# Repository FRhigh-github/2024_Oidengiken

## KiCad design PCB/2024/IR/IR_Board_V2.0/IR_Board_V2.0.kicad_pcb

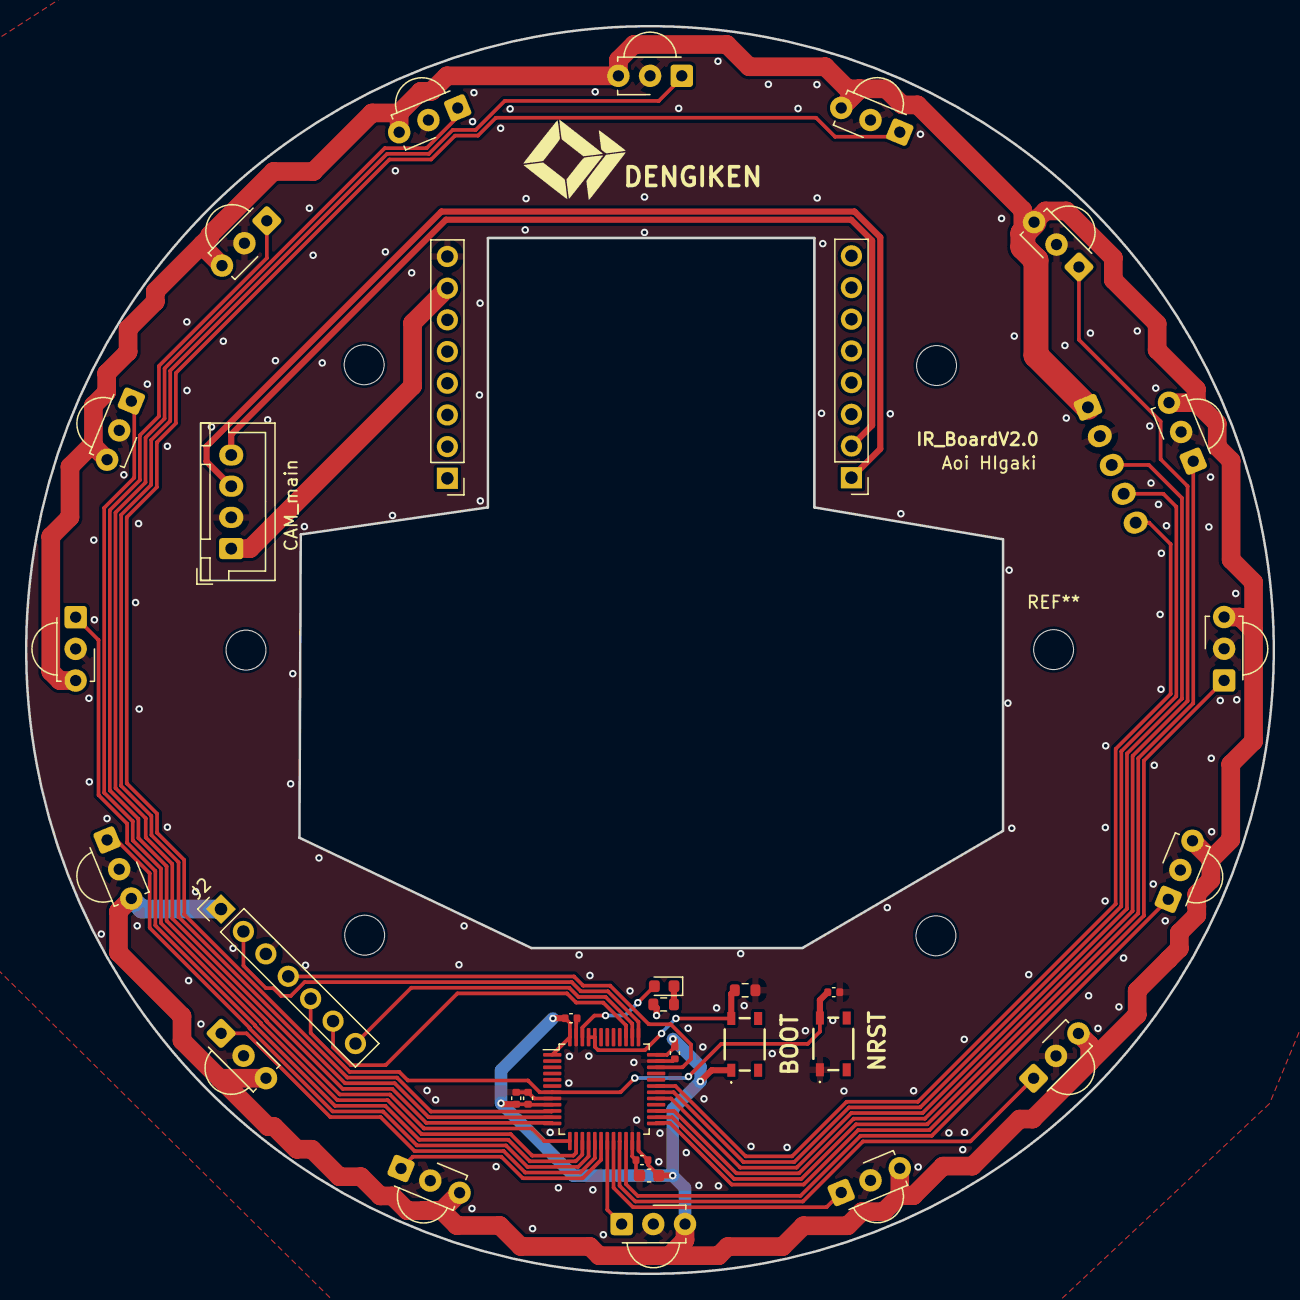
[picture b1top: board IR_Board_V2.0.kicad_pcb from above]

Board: 2 copper layers, 100.0 x 100.0 mm, 34 parts (1 on the bottom side), 32 nets.

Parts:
BOOT: BOOT; SKRPABE010
C1, C3, C5, C7: 0.1u; C_0402_1005Metric
C2: 0.01u; C_0402_1005Metric
C4: 1u; C_0402_1005Metric
C6: 4.7uf; C_0603_1608Metric
CAM_main: Conn_01x04_Socket; JST_XH_B4B-XH-A_1x04_P2.50mm_Vertical
D1: LED; LED_0603_1608Metric
IR_Main: Main,IR; JST_XH_B5B-XH-A_1x05_P2.50mm_Vertical
J2: PC; PinHeader_1x07_P2.54mm_Vertical
J4, J5: Conn_01x08_Male; PinHeader_1x08_P2.54mm_Vertical
NRST: NRST; SKRPABE010
R3: 100; R_0603_1608Metric
R4: R_Small; R_0603_1608Metric
U1: STM32F303C8Tx; LQFP-48_7x7mm_P0.5mm
U2, U3, U4, U5, U6, U7, U8, U9, U10, U11, U12, U13, U14, U15, U16, U17: TSSP58038; Vishay_MINICAST-3Pin

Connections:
+3.3V: BOOT.1, C1.1, C2.1, C3.1, C4.1, C5.1, C6.1, IR_Main.1, J2.1, U1.1 (VBAT), U1.9 (VDDA), U1.24 (VDD), U1.36 (VDD), U1.48 (VDD), U2.3 (Vs), U3.3 (Vs), U4.3 (Vs), U5.3 (Vs), U6.3 (Vs), U7.3 (Vs), U8.3 (Vs), U9.3 (Vs), U10.3 (Vs), U11.3 (Vs), U12.3 (Vs), U13.3 (Vs), U14.3 (Vs), U15.3 (Vs), U16.3 (Vs), U17.3 (Vs)
+5V: CAM_main.1, J5.7
BOOT: BOOT.2, R4.1, U1.44 (BOOT0), U1.45 (PB8)
CAMRX: CAM_main.3, J4.1
CAMTX: CAM_main.4, J4.2
GND: C1.2, C2.2, C3.2, C4.2, C5.2, C6.2, C7.2, CAM_main.2, IR_Main.2, J2.3, J5.8, NRST.1, R3.2, R4.2, U1.8 (VSSA), U1.23 (VSS), U1.35 (VSS), U1.47 (VSS), U2.2 (GND), U3.2 (GND), U4.2 (GND), U5.2 (GND), U6.2 (GND), U7.2 (GND), U8.2 (GND), U9.2 (GND), U10.2 (GND), U11.2 (GND), U12.2 (GND), U13.2 (GND), U14.2 (GND), U15.2 (GND), U16.2 (GND), U17.2 (GND)
GPIO0: U1.10 (PA0), U9.1 (OUT)
GPIO1: U1.11 (PA1), U2.1 (OUT)
GPIO2: U1.12 (PA2), U8.1 (OUT)
GPIO3: U1.13 (PA3), U6.1 (OUT)
GPIO4: U1.14 (PA4), U7.1 (OUT)
GPIO5: U1.15 (PA5), U3.1 (OUT)
GPIO6: U1.16 (PA6), U17.1 (OUT)
GPIO7: U1.17 (PA7), U16.1 (OUT)
GPIO8: U1.18 (PB0), U15.1 (OUT)
GPIO9: U1.19 (PB1), U4.1 (OUT)
GPIO10: U1.20 (PB2), U14.1 (OUT)
GPIO11: U1.21 (PB10), U13.1 (OUT)
GPIO12: U1.22 (PB11), U12.1 (OUT)
GPIO13: U1.25 (PB12), U5.1 (OUT)
GPIO14: U1.26 (PB13), U11.1 (OUT)
GPIO15: U1.27 (PB14), U10.1 (OUT)
NRST: C7.1, J2.5, NRST.2, U1.7 (NRST)
unnamed: D1.1 (K), R3.1
SWCLK: J2.2, U1.37 (PA14)
SWDIO: J2.4, U1.34 (PA13)
UI_LED: D1.2 (A), U1.46 (PB9)
USART1_CK: IR_Main.3, U1.29 (PA8)
USART1_RX: IR_Main.5, U1.31 (PA10)
USART1_TX: IR_Main.4, U1.30 (PA9)
USART2_RX: J2.7, U1.38 (PA15)
USART2_TX: J2.6, U1.39 (PB3)

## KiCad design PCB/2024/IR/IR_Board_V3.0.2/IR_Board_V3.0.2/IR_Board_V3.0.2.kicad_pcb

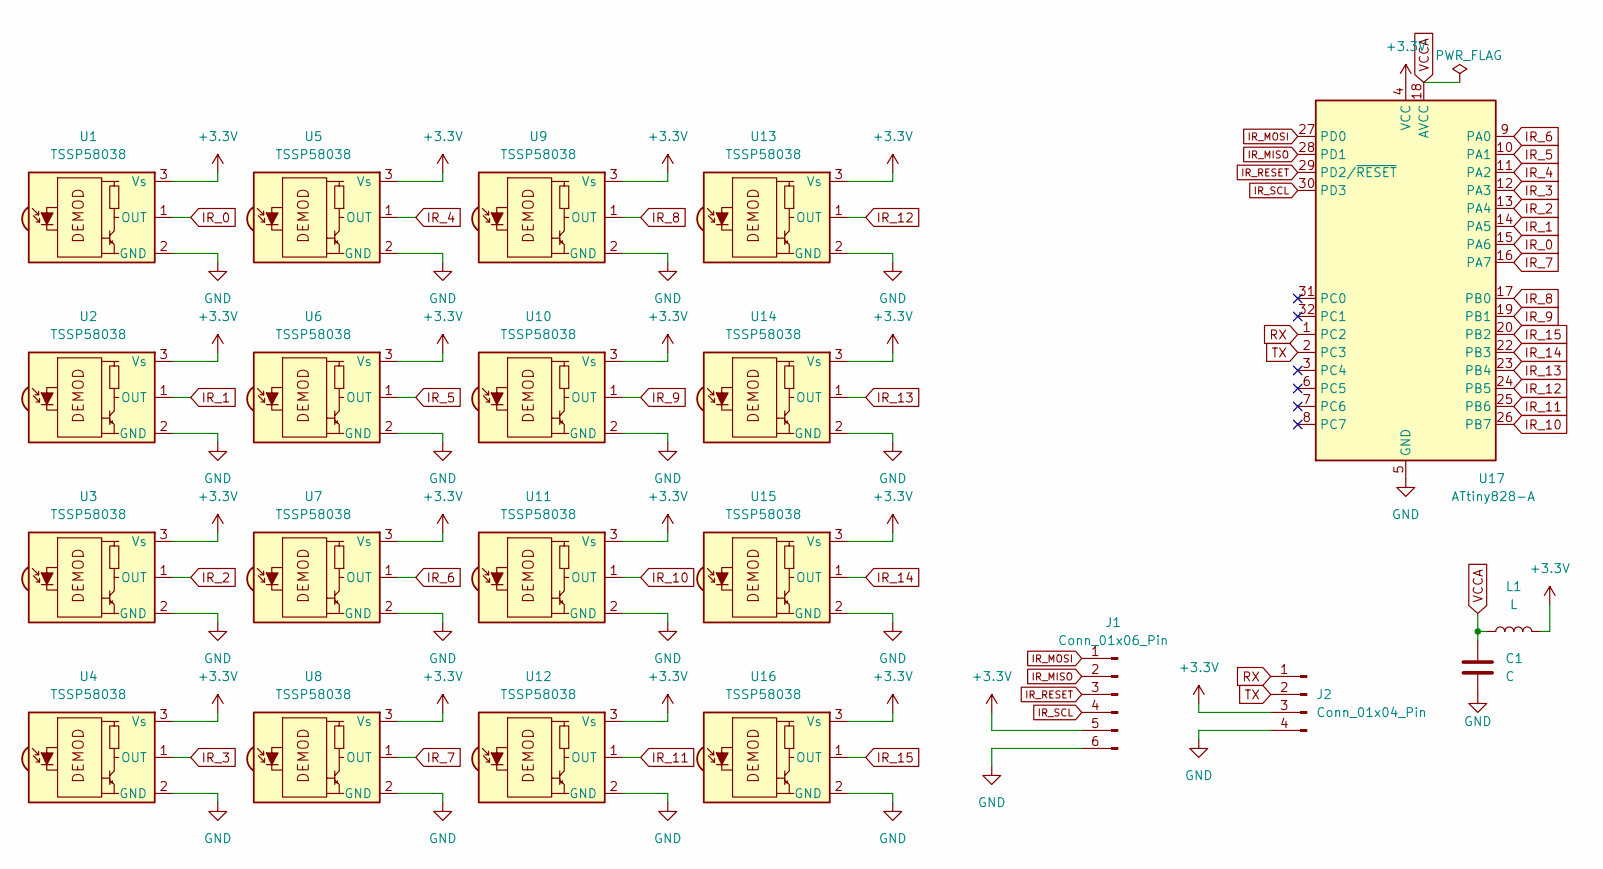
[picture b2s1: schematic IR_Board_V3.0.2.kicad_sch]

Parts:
C1: C; C_0603_1608Metric
J1: Conn_01x06_Pin; PinHeader_1x06_P2.54mm_Horizontal
J2: Conn_01x04_Pin; JST_XH_B4B-XH-A_1x04_P2.50mm_Vertical
L1: L; L_Axial_L12.0mm_D5.0mm_P15.24mm_Horizontal_Fastron_MISC
U1, U2, U3, U4, U5, U6, U7, U8, U9, U10, U11, U12, U13, U14, U15, U16: TSSP58038; Vishay_MINICAST-3Pin
U17: ATtiny828-A; TQFP-32_7x7mm_P0.8mm

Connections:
+3.3V: J1.5, J2.3, L1.2, U1.3 (Vs), U2.3 (Vs), U3.3 (Vs), U4.3 (Vs), U5.3 (Vs), U6.3 (Vs), U7.3 (Vs), U8.3 (Vs), U9.3 (Vs), U10.3 (Vs), U11.3 (Vs), U12.3 (Vs), U13.3 (Vs), U14.3 (Vs), U15.3 (Vs), U16.3 (Vs), U17.4 (VCC)
GND: C1.2, J1.6, J2.4, U1.2 (GND), U2.2 (GND), U3.2 (GND), U4.2 (GND), U5.2 (GND), U6.2 (GND), U7.2 (GND), U8.2 (GND), U9.2 (GND), U10.2 (GND), U11.2 (GND), U12.2 (GND), U13.2 (GND), U14.2 (GND), U15.2 (GND), U16.2 (GND), U17.5 (GND), U17.21 (GND)
IR_0: U1.1 (OUT), U17.15 (PA6)
IR_1: U2.1 (OUT), U17.14 (PA5)
IR_2: U3.1 (OUT), U17.13 (PA4)
IR_3: U4.1 (OUT), U17.12 (PA3)
IR_4: U5.1 (OUT), U17.11 (PA2)
IR_5: U6.1 (OUT), U17.10 (PA1)
IR_6: U7.1 (OUT), U17.9 (PA0)
IR_7: U8.1 (OUT), U17.16 (PA7)
IR_8: U9.1 (OUT), U17.17 (PB0)
IR_9: U10.1 (OUT), U17.19 (PB1)
IR_10: U11.1 (OUT), U17.26 (PB7)
IR_11: U12.1 (OUT), U17.25 (PB6)
IR_12: U13.1 (OUT), U17.24 (PB5)
IR_13: U14.1 (OUT), U17.23 (PB4)
IR_14: U15.1 (OUT), U17.22 (PB3)
IR_15: U16.1 (OUT), U17.20 (PB2)
IR_MISO: J1.2, U17.28 (PD1)
IR_MOSI: J1.1, U17.27 (PD0)
IR_RESET: J1.3, U17.29 (PD2/~RESET)
IR_SCL: J1.4, U17.30 (PD3)
RX: J2.1, U17.1 (PC2)
TX: J2.2, U17.2 (PC3)
VCCA: C1.1, L1.1, U17.18 (AVCC)

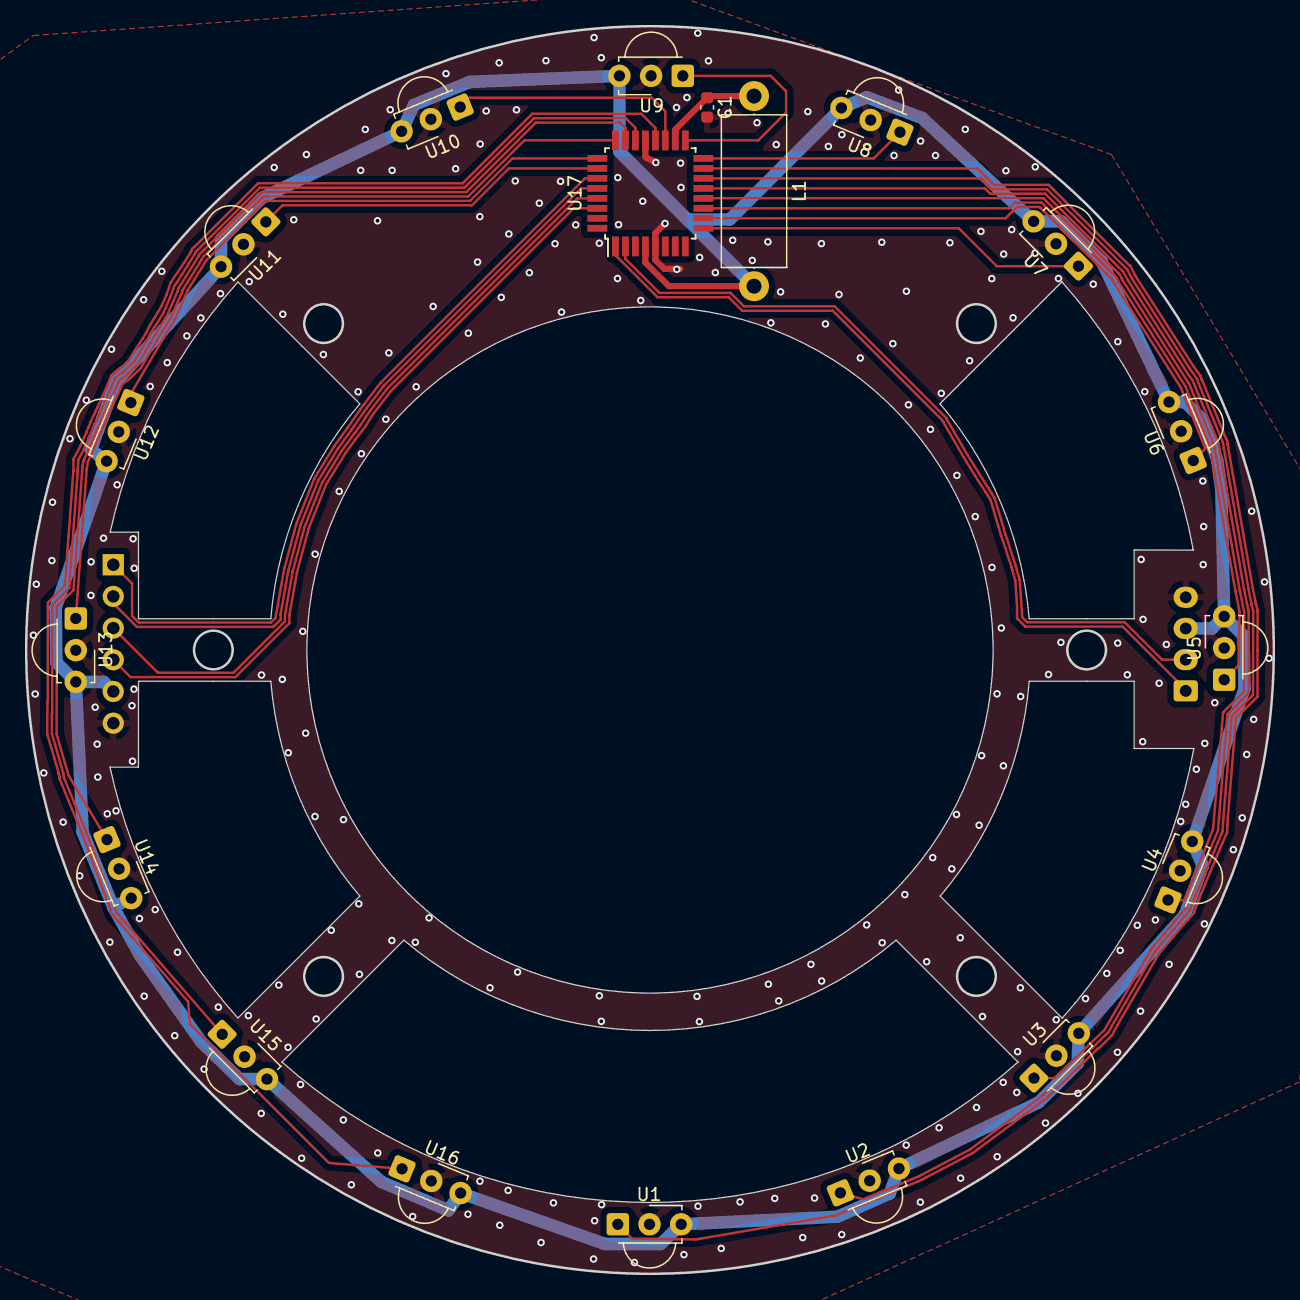
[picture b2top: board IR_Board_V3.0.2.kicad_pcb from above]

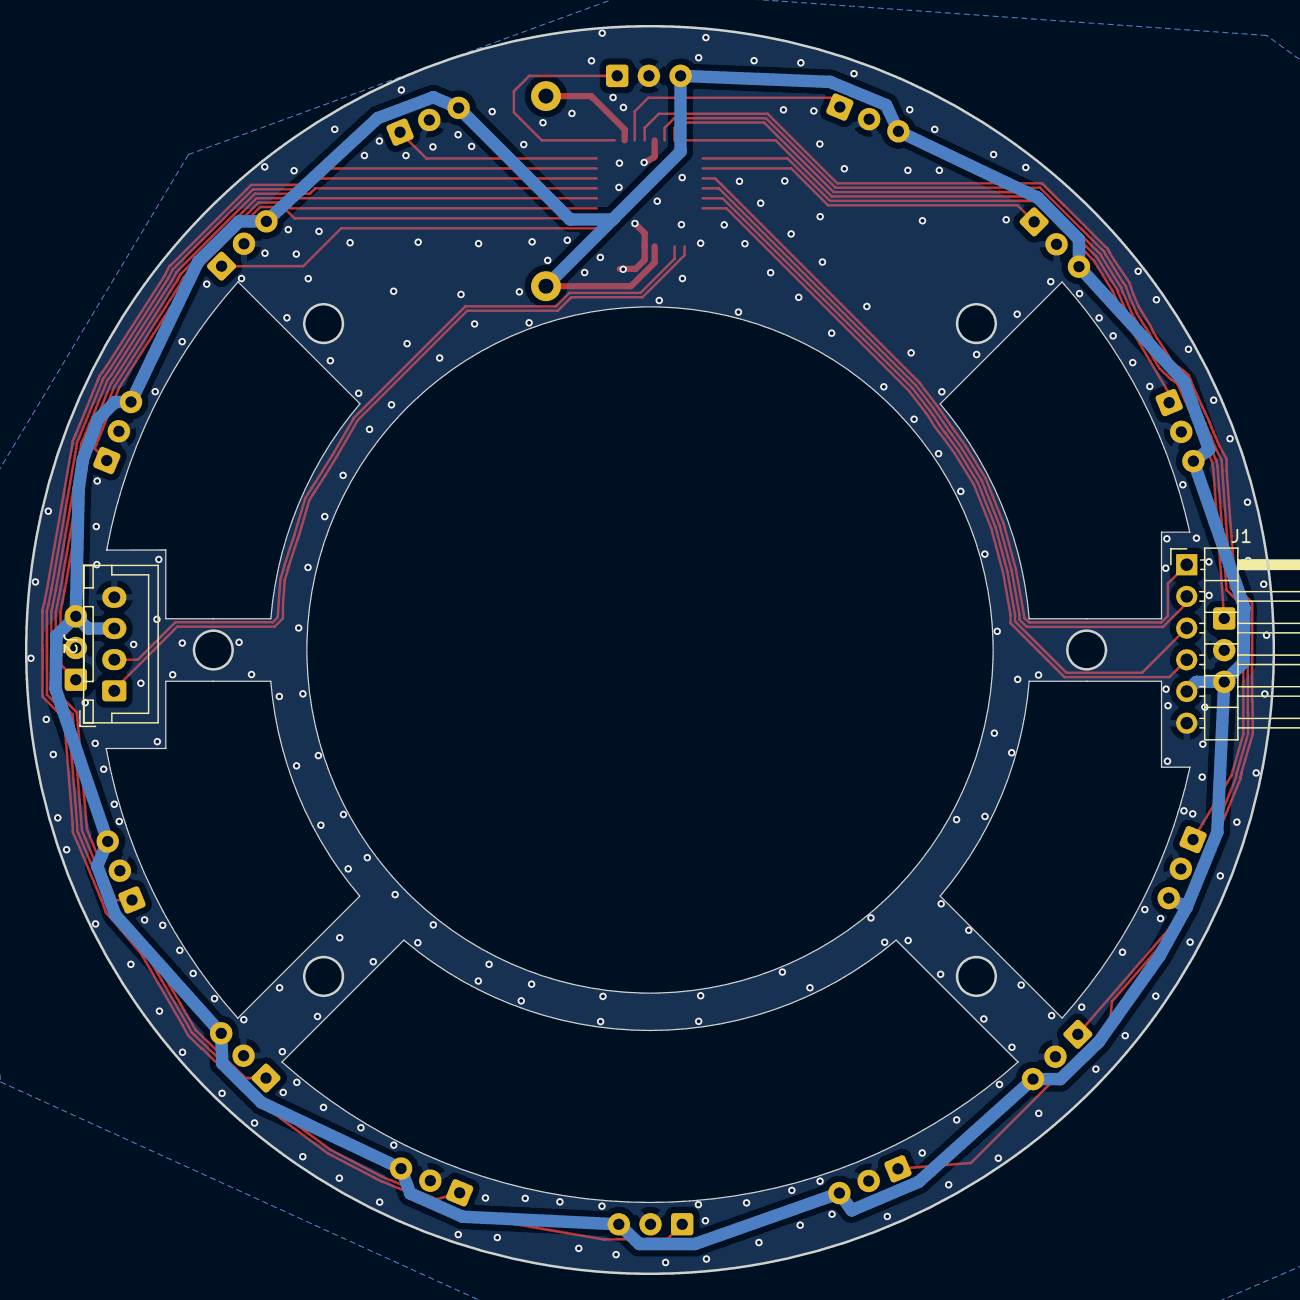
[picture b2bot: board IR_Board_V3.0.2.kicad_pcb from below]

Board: 2 copper layers, 100.0 x 100.0 mm, 21 parts (2 on the bottom side), 25 nets.

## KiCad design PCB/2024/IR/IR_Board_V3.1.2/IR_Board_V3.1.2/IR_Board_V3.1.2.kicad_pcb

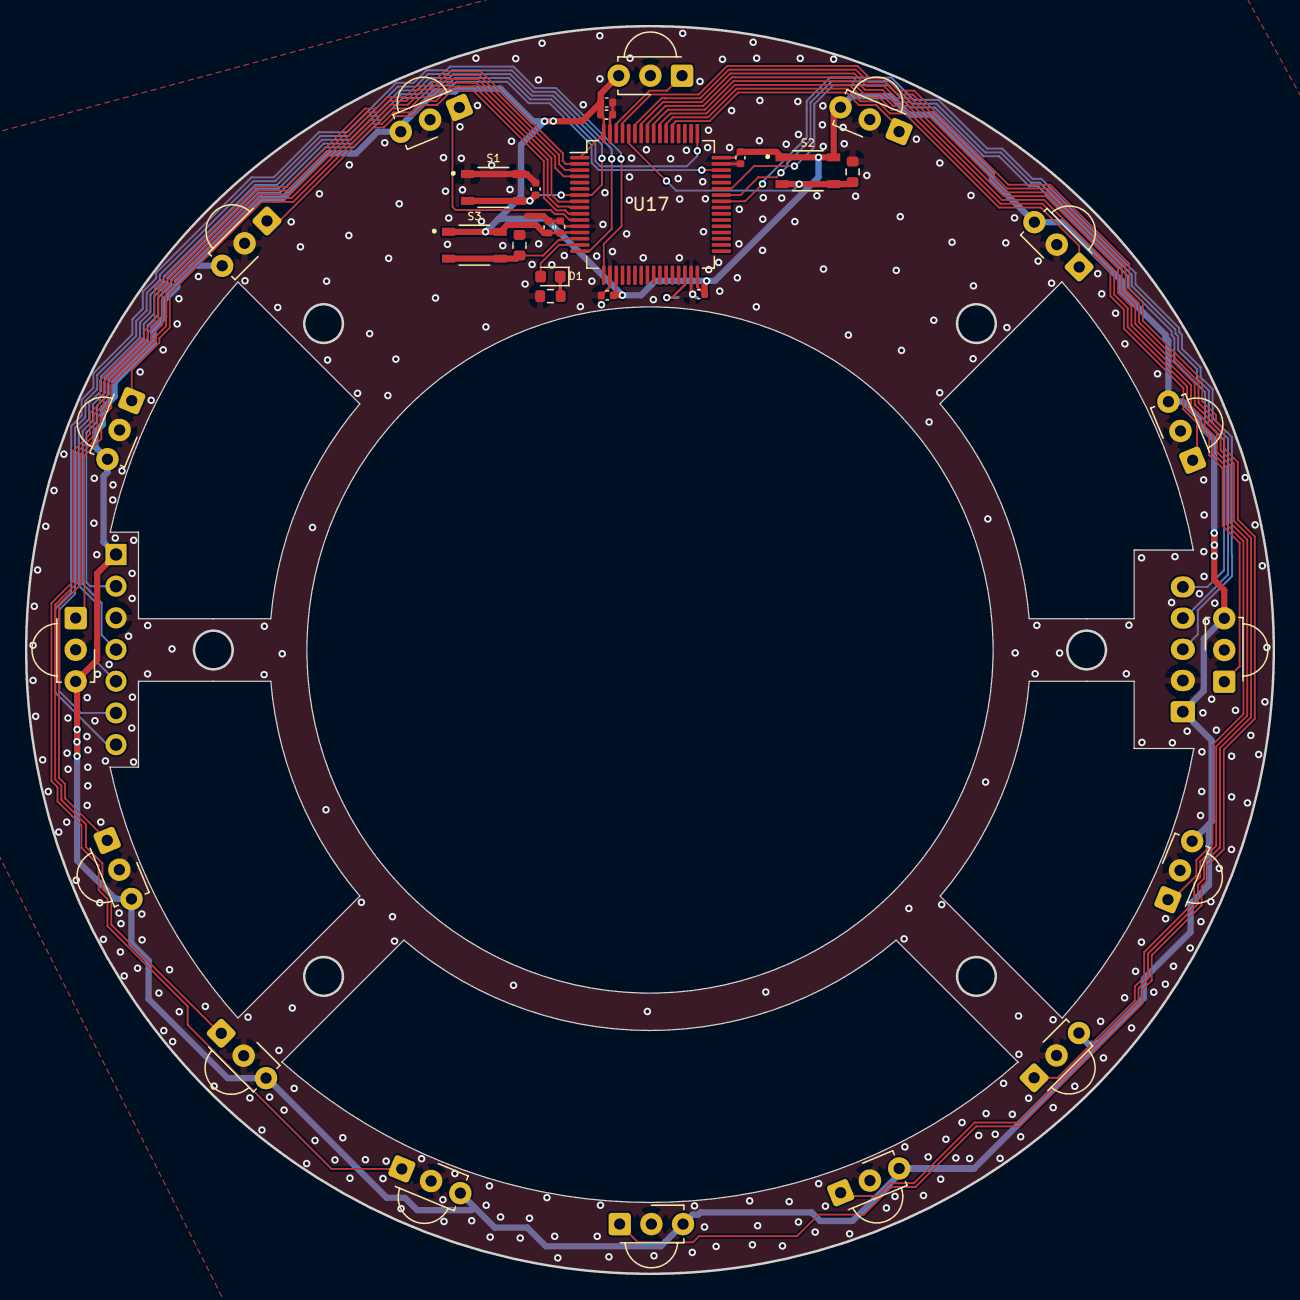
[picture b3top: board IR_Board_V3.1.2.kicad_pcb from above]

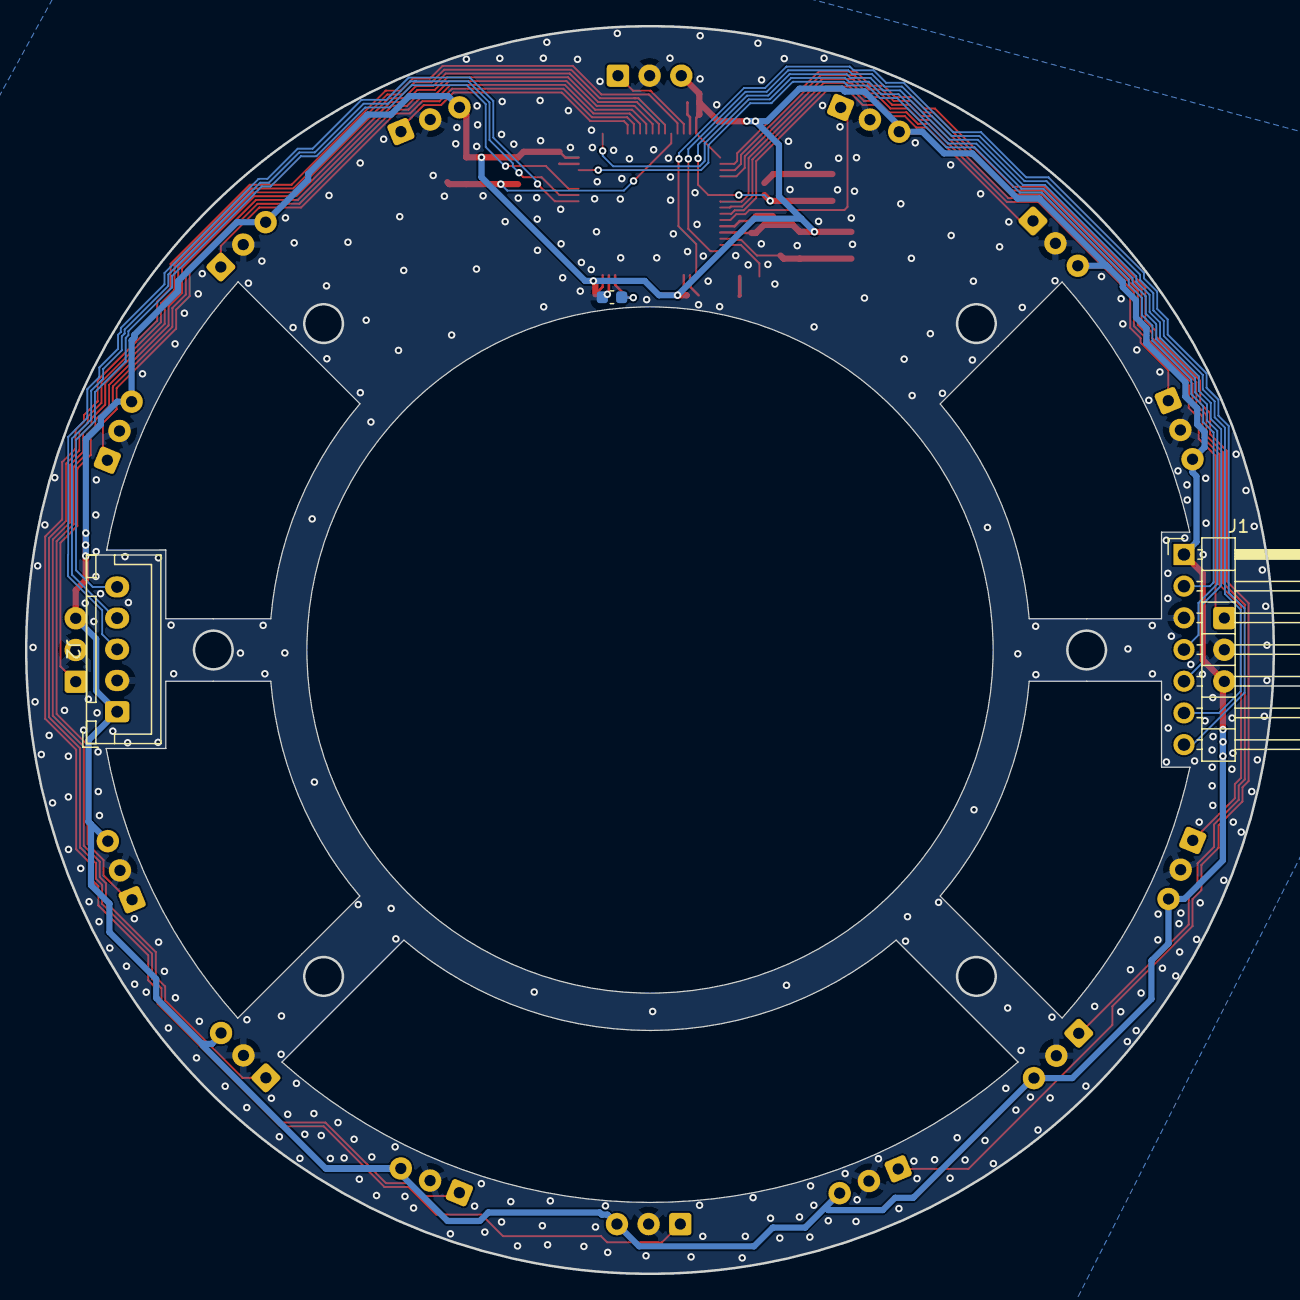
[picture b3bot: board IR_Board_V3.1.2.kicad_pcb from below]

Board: 2 copper layers, 100.0 x 100.0 mm, 35 parts (3 on the bottom side), 31 nets.

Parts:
C1, C2, C4, C6, C8, C10: 0.1u; C_0402_1005Metric
C3: 2.2u; C_0603_1608Metric
C5, C7: 1u; C_0402_1005Metric
D1: LED; LED_0603_1608Metric
J1: PC; PinHeader_1x07_P2.54mm_Horizontal
J2: Main; JST_XH_B5B-XH-A_1x05_P2.50mm_Vertical
R1, R2: 10k; R_0603_1608Metric
R3: 100; R_0603_1608Metric
S1, S2, S3: SKRPABE010; SW_SKRPABE010
U1, U2, U3, U4, U5, U6, U7, U8, U9, U10, U11, U12, U13, U14, U15, U16: TSSP58038; Vishay_MINICAST-3Pin
U17: STM32F446RETx; LQFP-64_10x10mm_P0.5mm

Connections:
+3.3V: C1.1, C2.1, C4.1, C5.1, C6.1, C7.1, C8.1, J1.1, J2.1, S2.1, S2.2, S3.1, S3.2, U1.3 (Vs), U2.3 (Vs), U3.3 (Vs), U4.3 (Vs), U5.3 (Vs), U6.3 (Vs), U7.3 (Vs), U8.3 (Vs), U9.3 (Vs), U10.3 (Vs), U11.3 (Vs), U12.3 (Vs), U13.3 (Vs), U14.3 (Vs), U15.3 (Vs), U16.3 (Vs), U17.1 (VBAT), U17.13 (VDDA), U17.19 (VDD), U17.32 (VDD), U17.48 (VDD), U17.64 (VDD)
BOOT: R1.1, S2.3, S2.4, U17.60 (BOOT0)
GND: C1.2, C2.2, C3.2, C4.2, C5.2, C6.2, C7.2, C8.2, C10.2, J1.3, J2.2, R1.2, R2.2, R3.2, S1.1, S1.2, U1.2 (GND), U2.2 (GND), U3.2 (GND), U4.2 (GND), U5.2 (GND), U6.2 (GND), U7.2 (GND), U8.2 (GND), U9.2 (GND), U10.2 (GND), U11.2 (GND), U12.2 (GND), U13.2 (GND), U14.2 (GND), U15.2 (GND), U16.2 (GND), U17.12 (VSSA), U17.18 (VSS), U17.31 (VSS), U17.47 (VSS), U17.63 (VSS)
IR_0: U1.1 (OUT), U17.61 (PB8)
IR_1: U2.1 (OUT), U17.59 (PB7)
IR_2: U3.1 (OUT), U17.58 (PB6)
IR_3: U4.1 (OUT), U17.57 (PB5)
IR_4: U5.1 (OUT), U17.56 (PB4)
IR_5: U6.1 (OUT), U17.55 (PB3)
IR_6: U7.1 (OUT), U17.54 (PD2)
IR_7: U8.1 (OUT), U17.53 (PC12)
IR_8: U9.1 (OUT), U17.62 (PB9)
IR_9: U10.1 (OUT), U17.11 (PC3)
IR_10: U11.1 (OUT), U17.10 (PC2)
IR_11: U12.1 (OUT), U17.9 (PC1)
IR_12: U13.1 (OUT), U17.8 (PC0)
IR_13: U14.1 (OUT), U17.4 (PC15)
IR_14: U15.1 (OUT), U17.3 (PC14)
IR_15: U16.1 (OUT), U17.2 (PC13)
NRST: C10.1, J1.5, S1.3, S1.4, U17.7 (NRST)
unnamed: D1.1 (K), R3.1
SWCLK: J1.2, U17.46 (PA13)
SWDIO: J1.4, U17.49 (PA14)
UI_LED: D1.2 (A), U17.15 (PA1)
UI_SW: R2.1, S3.3, S3.4, U17.14 (PA0)
USART1_CK: J2.3, U17.41 (PA8)
USART1_RX: J2.5, U17.43 (PA10)
USART1_TX: J2.4, U17.42 (PA9)
USART2_RX_USB: J1.7, U17.17 (PA3)
USART2_TX_USB: J1.6, U17.16 (PA2)
VCAP: C3.1, U17.30 (VCAP_1)

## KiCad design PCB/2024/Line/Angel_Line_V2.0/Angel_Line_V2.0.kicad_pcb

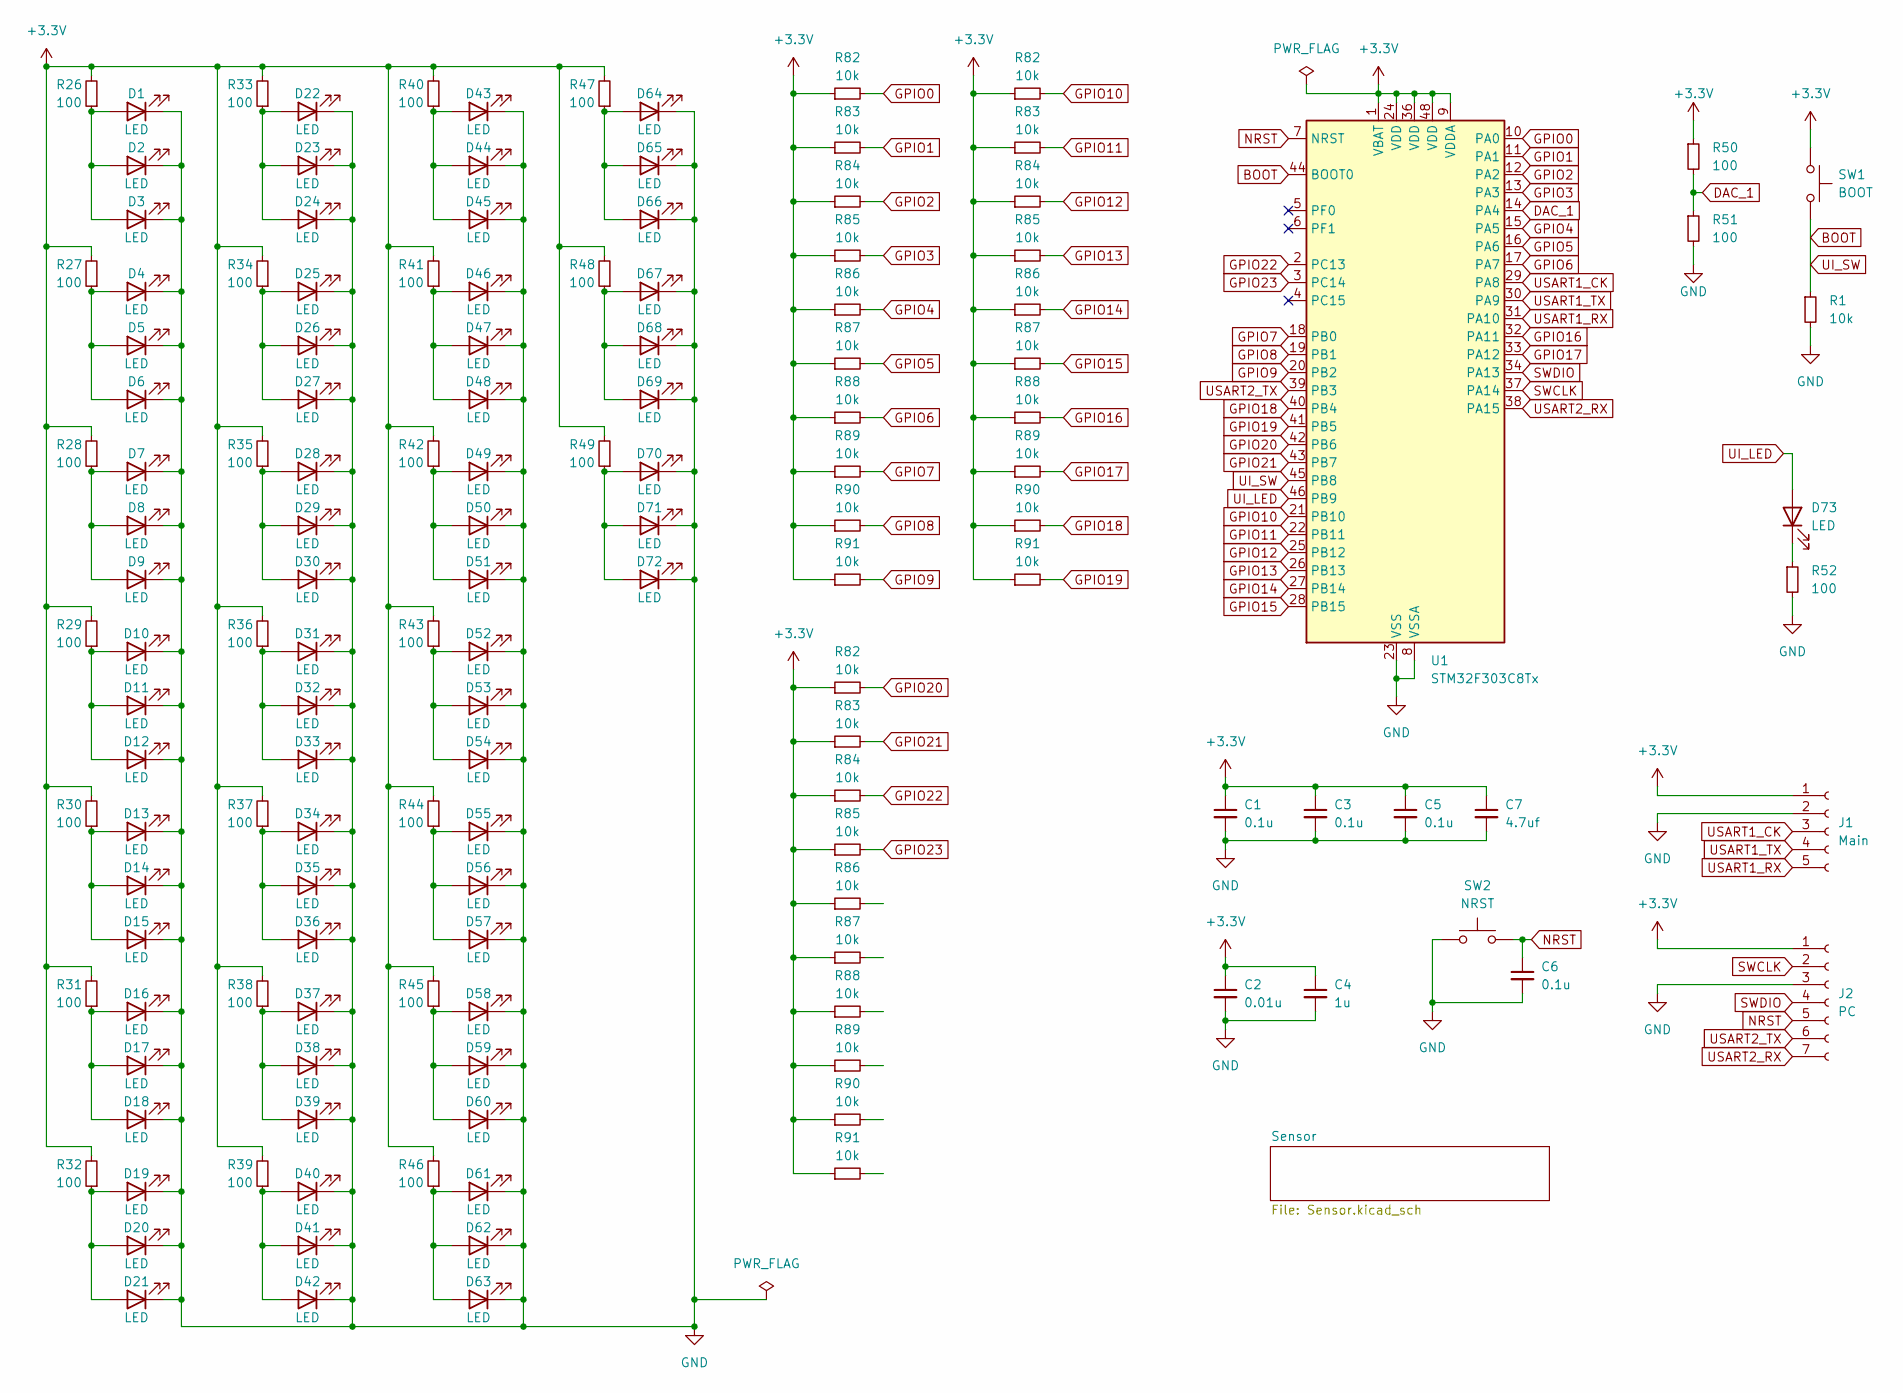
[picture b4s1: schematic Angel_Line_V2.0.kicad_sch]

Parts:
C1, C3, C5, C6: 0.1u; C_0402_1005Metric
C2: 0.01u; C_0402_1005Metric
C4: 1u; C_0402_1005Metric
C7: 4.7uf; C_0603_1608Metric
D1, D2, D3, D4, D5, D6, D7, D8, D9, D10, D11, D12, D13, D14, D15, D16, D17, D18, D19, D20, D21, D22, D23, D24, D25, D26, D27, D28, D29, D30, D31, D32, D33, D34, D35, D36, D37, D38, D39, D40, D41, D42, D43, D44, D45, D46, D47, D48, D49, D50, D51, D52, D53, D54, D55, D56, D57, D58, D59, D60, D61, D62, D63, D64, D65, D66, D67, D68, D69, D70, D71, D72, D73: LED; LED_0603_1608Metric
J1: Main; JST_XH_B5B-XH-A_1x05_P2.50mm_Vertical
J2: PC; JST_XH_B7B-XH-A_1x07_P2.50mm_Vertical
R1, R82, R83, R84, R85, R86, R87, R88, R89, R90, R91: 10k; R_0603_1608Metric
R26, R27, R28, R29, R30, R31, R32, R33, R34, R35, R36, R37, R38, R39, R40, R41, R42, R43, R44, R45, R46, R47, R48, R49, R50, R51, R52: 100; R_0603_1608Metric
SW1: BOOT; SW_SKRPABE010
SW2: NRST; SW_SKRPABE010
U1: STM32F303C8Tx; LQFP-48_7x7mm_P0.5mm

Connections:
+3.3V: C1.1, C2.1, C3.1, C4.1, C5.1, C7.1, J1.1, J2.1, R26.2, R27.2, R28.2, R29.2, R30.2, R31.2, R32.2, R33.2, R34.2, R35.2, R36.2, R37.2, R38.2, R39.2, R40.2, R41.2, R42.2, R43.2, R44.2, R45.2, R46.2, R47.2, R48.2, R49.2, R50.1, R82.1, R83.1, R84.1, R85.1, R86.1, R87.1, R88.1, R89.1, R90.1, R91.1, SW1.1, U1.1 (VBAT), U1.9 (VDDA), U1.24 (VDD), U1.36 (VDD), U1.48 (VDD); also elsewhere on the board
BOOT: R1.1, SW1.2, U1.44 (BOOT0), U1.45 (PB8); also elsewhere on the board
DAC_1: R50.2, R51.1, U1.14 (PA4); also elsewhere on the board
GND: C1.2, C2.2, C3.2, C4.2, C5.2, C6.2, C7.2, D1.1 (K), D2.1 (K), D3.1 (K), D4.1 (K), D5.1 (K), D6.1 (K), D7.1 (K), D8.1 (K), D9.1 (K), D10.1 (K), D11.1 (K), D12.1 (K), D13.1 (K), D14.1 (K), D15.1 (K), D16.1 (K), D17.1 (K), D18.1 (K), D19.1 (K), D20.1 (K), D21.1 (K), D22.1 (K), D23.1 (K), D24.1 (K), D25.1 (K), D26.1 (K), D27.1 (K), D28.1 (K), D29.1 (K), D30.1 (K), D31.1 (K), D32.1 (K), D33.1 (K), D34.1 (K), D35.1 (K), D36.1 (K), D37.1 (K), D38.1 (K), D39.1 (K), D40.1 (K), D41.1 (K), D42.1 (K), D43.1 (K), D44.1 (K), D45.1 (K), D46.1 (K), D47.1 (K), D48.1 (K), D49.1 (K), D50.1 (K), D51.1 (K), D52.1 (K), D53.1 (K), D54.1 (K), D55.1 (K), D56.1 (K), D57.1 (K), D58.1 (K), D59.1 (K), D60.1 (K), D61.1 (K), D62.1 (K), D63.1 (K), D64.1 (K), D65.1 (K), D66.1 (K), D67.1 (K), D68.1 (K), D69.1 (K), D70.1 (K), D71.1 (K), D72.1 (K), J1.2, J2.3, R1.2, R51.2, R52.2, SW2.1, U1.8 (VSSA), U1.23 (VSS), U1.35 (VSS), U1.47 (VSS); also elsewhere on the board
GPIO0: R82.2, U1.10 (PA0); also elsewhere on the board
GPIO1: R83.2, U1.11 (PA1); also elsewhere on the board
GPIO2: R84.2, U1.12 (PA2); also elsewhere on the board
GPIO3: R85.2, U1.13 (PA3); also elsewhere on the board
GPIO4: R86.2, U1.15 (PA5); also elsewhere on the board
GPIO5: R87.2, U1.16 (PA6); also elsewhere on the board
GPIO6: R88.2, U1.17 (PA7); also elsewhere on the board
GPIO7: R89.2, U1.18 (PB0); also elsewhere on the board
GPIO8: R90.2, U1.19 (PB1); also elsewhere on the board
GPIO9: R91.2, U1.20 (PB2); also elsewhere on the board
GPIO10: R82.2, U1.21 (PB10); also elsewhere on the board
GPIO11: R83.2, U1.22 (PB11); also elsewhere on the board
GPIO12: R84.2, U1.25 (PB12); also elsewhere on the board
GPIO13: R85.2, U1.26 (PB13); also elsewhere on the board
GPIO14: R86.2, U1.27 (PB14); also elsewhere on the board
GPIO15: R87.2, U1.28 (PB15); also elsewhere on the board
GPIO16: R88.2, U1.32 (PA11); also elsewhere on the board
GPIO17: R89.2, U1.33 (PA12); also elsewhere on the board
GPIO18: R90.2, U1.40 (PB4); also elsewhere on the board
GPIO19: R91.2, U1.41 (PB5); also elsewhere on the board
GPIO20: R82.2, U1.42 (PB6); also elsewhere on the board
GPIO21: R83.2, U1.43 (PB7); also elsewhere on the board
GPIO22: R84.2, U1.2 (PC13); also elsewhere on the board
GPIO23: R85.2, U1.3 (PC14); also elsewhere on the board
NRST: C6.1, J2.5, SW2.2, U1.7 (NRST); also elsewhere on the board
unnamed: D1.2 (A), D2.2 (A), D3.2 (A), R26.1
unnamed: D4.2 (A), D5.2 (A), D6.2 (A), R27.1
unnamed: D7.2 (A), D8.2 (A), D9.2 (A), R28.1
unnamed: D10.2 (A), D11.2 (A), D12.2 (A), R29.1
unnamed: D13.2 (A), D14.2 (A), D15.2 (A), R30.1
unnamed: D16.2 (A), D17.2 (A), D18.2 (A), R31.1
unnamed: D19.2 (A), D20.2 (A), D21.2 (A), R32.1
unnamed: D22.2 (A), D23.2 (A), D24.2 (A), R33.1
unnamed: D25.2 (A), D26.2 (A), D27.2 (A), R34.1
unnamed: D28.2 (A), D29.2 (A), D30.2 (A), R35.1
unnamed: D31.2 (A), D32.2 (A), D33.2 (A), R36.1
unnamed: D34.2 (A), D35.2 (A), D36.2 (A), R37.1
unnamed: D37.2 (A), D38.2 (A), D39.2 (A), R38.1
unnamed: D40.2 (A), D41.2 (A), D42.2 (A), R39.1
unnamed: D43.2 (A), D44.2 (A), D45.2 (A), R40.1
unnamed: D46.2 (A), D47.2 (A), D48.2 (A), R41.1
unnamed: D49.2 (A), D50.2 (A), D51.2 (A), R42.1
unnamed: D52.2 (A), D53.2 (A), D54.2 (A), R43.1
unnamed: D55.2 (A), D56.2 (A), D57.2 (A), R44.1
unnamed: D58.2 (A), D59.2 (A), D60.2 (A), R45.1
unnamed: D61.2 (A), D62.2 (A), D63.2 (A), R46.1
unnamed: D64.2 (A), D65.2 (A), D66.2 (A), R47.1
unnamed: D67.2 (A), D68.2 (A), D69.2 (A), R48.1
unnamed: D70.2 (A), D71.2 (A), D72.2 (A), R49.1
unnamed: D73.1 (K), R52.1
SWCLK: J2.2, U1.37 (PA14); also elsewhere on the board
SWDIO: J2.4, U1.34 (PA13); also elsewhere on the board
UI_LED: D73.2 (A), U1.46 (PB9)
USART1_CK: J1.3, U1.29 (PA8); also elsewhere on the board
USART1_RX: J1.5, U1.31 (PA10); also elsewhere on the board
USART1_TX: J1.4, U1.30 (PA9); also elsewhere on the board
USART2_RX: J2.7, U1.38 (PA15); also elsewhere on the board
USART2_TX: J2.6, U1.39 (PB3); also elsewhere on the board
